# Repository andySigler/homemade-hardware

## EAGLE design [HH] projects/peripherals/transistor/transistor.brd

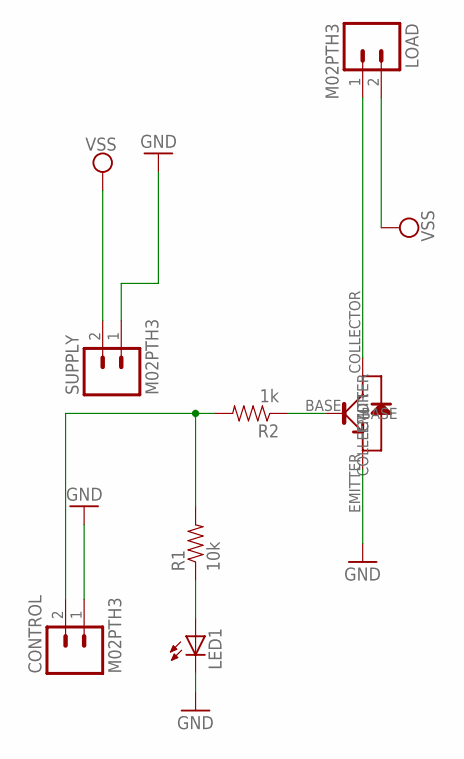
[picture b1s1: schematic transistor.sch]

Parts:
CONTROL: M02PTH3; 1X02_LONGPADS
LED1: LEDCHIPLED_0603; CHIPLED_0603
LOAD: M02PTH3; 1X02_LONGPADS
R1: 10k; 0603-RES
R2: 1k; 0603-RES
SUPPLY: M02PTH3; 1X02_LONGPADS
U$1: STB13007DT4; D2PAK-TO263

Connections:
COLLECTOR: LOAD.1, U$1.COLLECTOR
GND: CONTROL.1, LED1.C, SUPPLY.1, U$1.EMITTER
unnamed: LED1.A, R1.1
unnamed: R2.1, U$1.BASE
unnamed: CONTROL.2, R1.2, R2.2
VSS: LOAD.2, SUPPLY.2

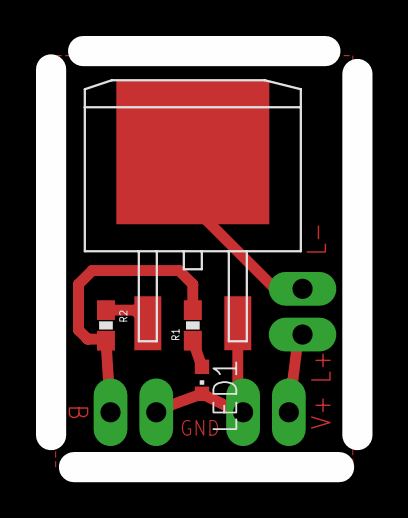
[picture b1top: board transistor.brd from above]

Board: 2 copper layers, 17.0 x 23.1 mm, 7 parts (0 on the bottom side), 6 nets.

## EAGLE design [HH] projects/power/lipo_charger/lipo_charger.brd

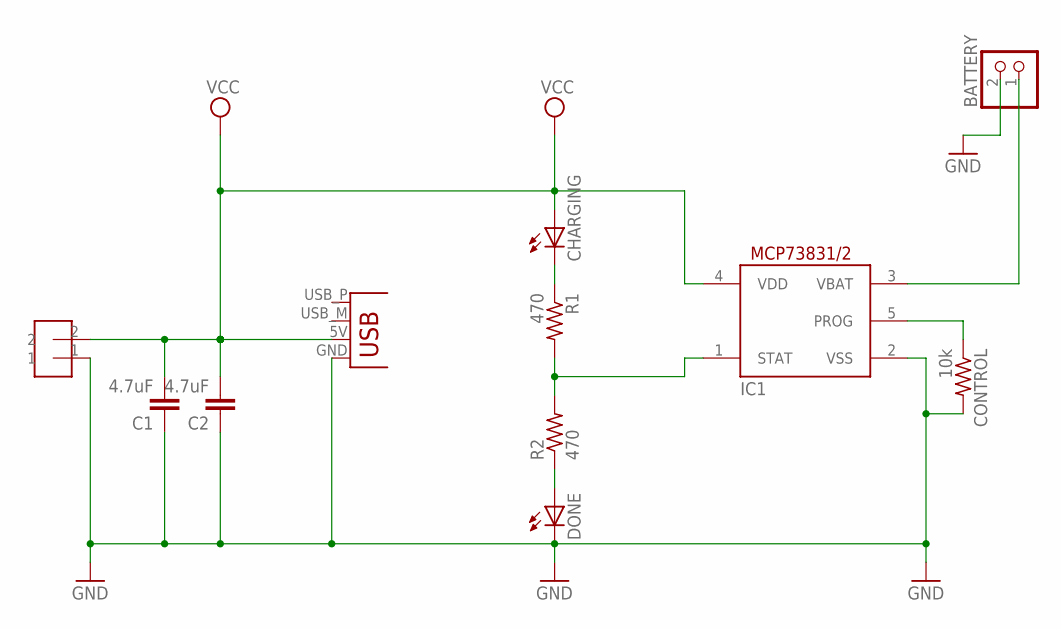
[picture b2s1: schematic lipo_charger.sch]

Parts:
BATTERY: JST_2PIN-SMT-RA; JST-PH-2-SMT-RA
C1, C2: 4.7uF; 0603-CAP
CHARGING: LEDCHIPLED_0603; CHIPLED_0603
CONTROL: 10k; R0603
DONE: LEDCHIPLED_0603; CHIPLED_0603
IC1: MCP73831/OT; SOT23-5L
JP1: USBPCB; USB-A-PCB
R1, R2: 470; R0603
U$1: HEADER-2

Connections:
GND: BATTERY.2 (1), C1.1, C2.1, CONTROL.2, DONE.C, IC1.2 (VSS), JP1.GND, U$1.1
unnamed: IC1.1 (STAT), R1.2, R2.2
unnamed: CHARGING.C, R1.1
unnamed: DONE.A, R2.1
unnamed: BATTERY.1 (2), IC1.3 (VBAT)
unnamed: CONTROL.1, IC1.5 (PROG)
VCC: C1.2, C2.2, CHARGING.A, IC1.4 (VDD), JP1.5V (VBUS), U$1.2

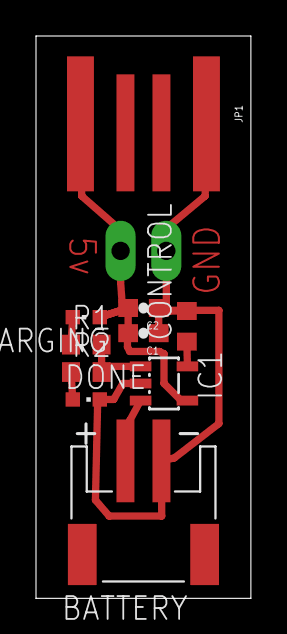
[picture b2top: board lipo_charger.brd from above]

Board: 2 copper layers, 11.9 x 31.2 mm, 11 parts (0 on the bottom side), 7 nets.

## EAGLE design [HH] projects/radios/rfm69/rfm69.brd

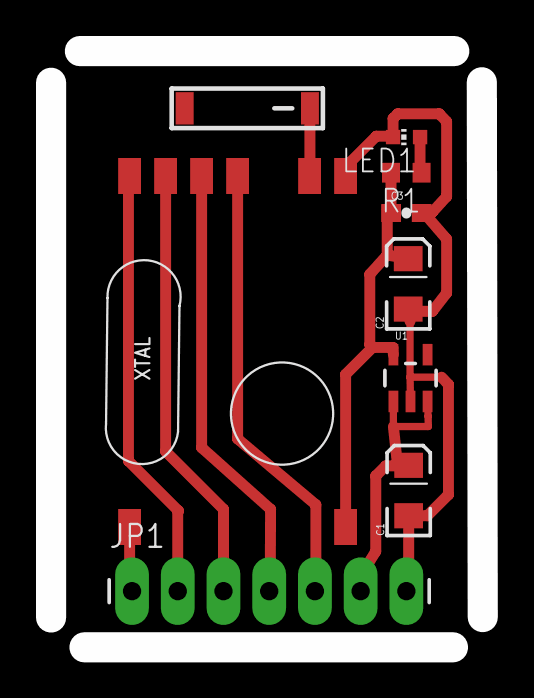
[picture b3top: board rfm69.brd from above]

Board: 2 copper layers, 24.0 x 33.1 mm, 9 parts (0 on the bottom side), 10 nets.

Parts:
C1, C2: EIA3216
C3: 0603-CAP
JP1: 1X07_LONGPADS
LED1: CHIP-LED0603
R1: 10k; R0603
U1: V_REG_LDOSMD; SOT23-5
U$1: 915MHZ-ANTENNA-SMD; 915MHZ-ANTENNA
U$5: RFM69; RFM69W-MINPADS

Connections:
D2: JP1.1, U$5.DIO0
D10_SS: JP1.2, U$5.NSS
D11_MOSI: JP1.3, U$5.MOSI
D12_MISO: JP1.4, U$5.MISO
D13_SCK: JP1.5, U$5.SCK
GND: C1.C, C2.C, C3.2, JP1.7, LED1.C, U1.2, U$5.GND
unnamed: U$1.SIGNAL, U$5.ANA
unnamed: LED1.A, R1.1
VCC: C2.A, C3.1, R1.2, U1.5, U$5.VDD
VSS: C1.A, JP1.6, U1.1, U1.3

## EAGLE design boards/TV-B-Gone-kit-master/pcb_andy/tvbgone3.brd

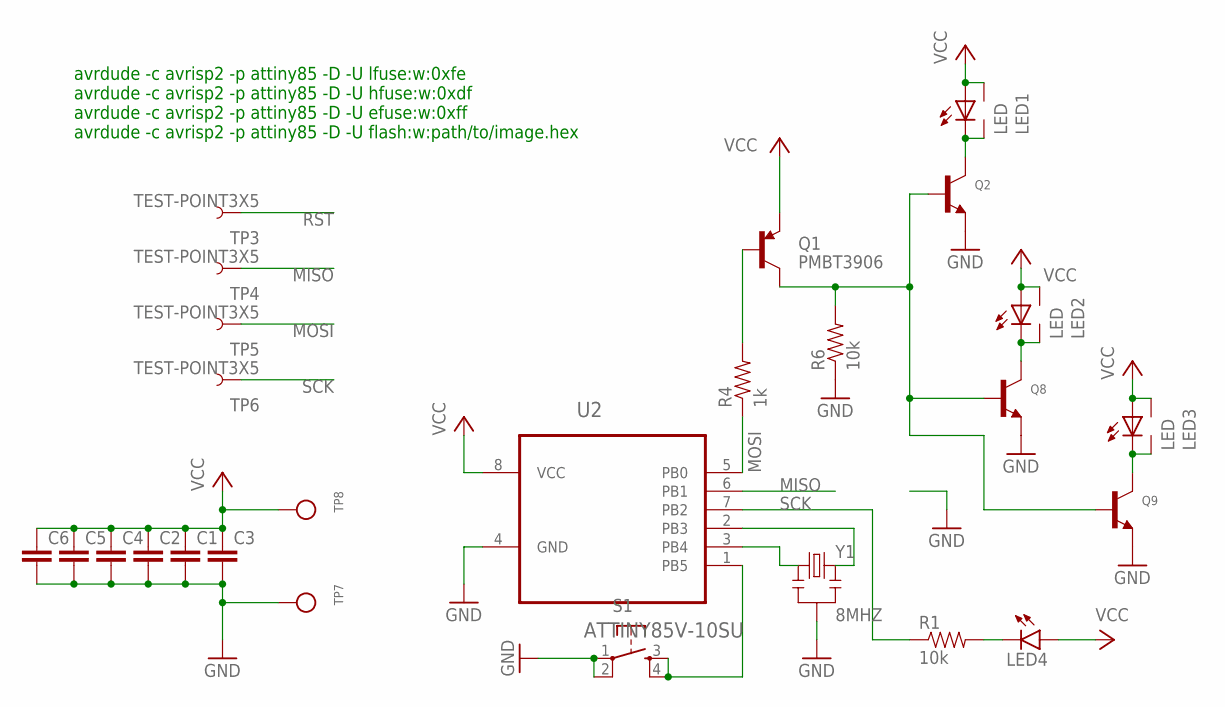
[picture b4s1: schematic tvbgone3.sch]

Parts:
C1, C2, C3, C4, C5, C6: CAP0603-CAP; 0603-CAP
LED1, LED2, LED3: LED; 5MM-SIDE
LED4: LED0603; LED-0603
Q1: PMBT3906; SOT23-3
Q2, Q8, Q9: TRANSISTOR_NPN; SOT-23-R
R1, R6: 10k; 0603-RES
R4: 1k; 0603-RES
S1: TAC_SWITCHSMD; TACTILE-SWITCH-SMD
TP3, TP4, TP5, TP6: TEST-POINT3X5; PAD.03X.05
TP7, TP8: TESTPOINTPAD; TESTPOINT_PAD_2MM
U2: ATTINY85V-10SU; SOIC127P798X216-8N
Y1: 8MHZ; RESONATOR-SMD

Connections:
GND: C1.2, C2.2, C3.2, C4.2, C5.2, C6.2, Q2.3-EMITTER (E), Q8.3-EMITTER (E), Q9.3-EMITTER (E), R6.1, S1.1, S1.2, TP7.P$1, U2.4 (GND), Y1.2
MISO: TP4.P$1, U2.6 (PB1)
MOSI: R4.1, TP5.P$1, U2.5 (PB0)
unnamed: U2.3 (PB4), Y1.1
unnamed: U2.2 (PB3), Y1.3
unnamed: LED4.C, R1.2
unnamed: LED1.K (C), LED1.K2 (C1), Q2.2-COLLECTOR (C)
unnamed: LED2.K (C), LED2.K2 (C1), Q8.2-COLLECTOR (C)
unnamed: Q1.1 (B), R4.2
unnamed: LED3.K (C), LED3.K2 (C1), Q9.2-COLLECTOR (C)
unnamed: Q1.3 (C), Q2.1-BASE (B), Q8.1-BASE (B), Q9.1-BASE (B), R6.2
RST: S1.3, S1.4, TP3.P$1, U2.1 (PB5)
SCK: R1.1, TP6.P$1, U2.7 (PB2)
VCC: C1.1, C2.1, C3.1, C4.1, C5.1, C6.1, LED1.A, LED1.A2 (A1), LED2.A, LED2.A2 (A1), LED3.A, LED3.A2 (A1), LED4.A, Q1.2 (E), TP8.P$1, U2.8 (VCC)

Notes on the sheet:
avrdude -c avrisp2 -p attiny85 -D -U lfuse:w:0xfe avrdude -c avrisp2 -p attiny85 -D -U hfuse:w:0xdf avrdude -c avrisp2 -p attiny85 -D -U efuse:w:0xff avrdude -c avrisp2 -p attiny85 -D -U flash:w:path/to/image.hex

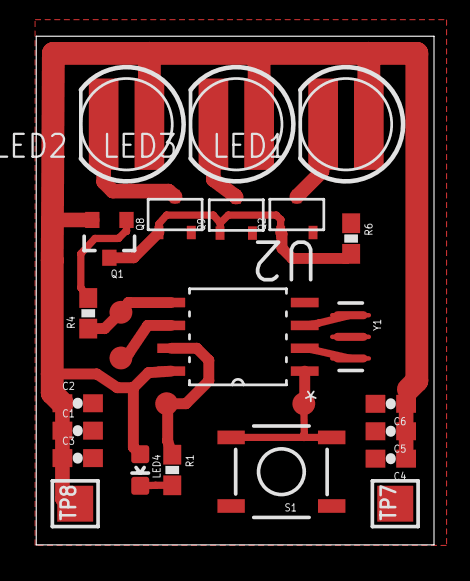
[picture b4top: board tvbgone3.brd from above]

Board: 2 copper layers, 22.1 x 28.3 mm, 26 parts (0 on the bottom side), 14 nets.

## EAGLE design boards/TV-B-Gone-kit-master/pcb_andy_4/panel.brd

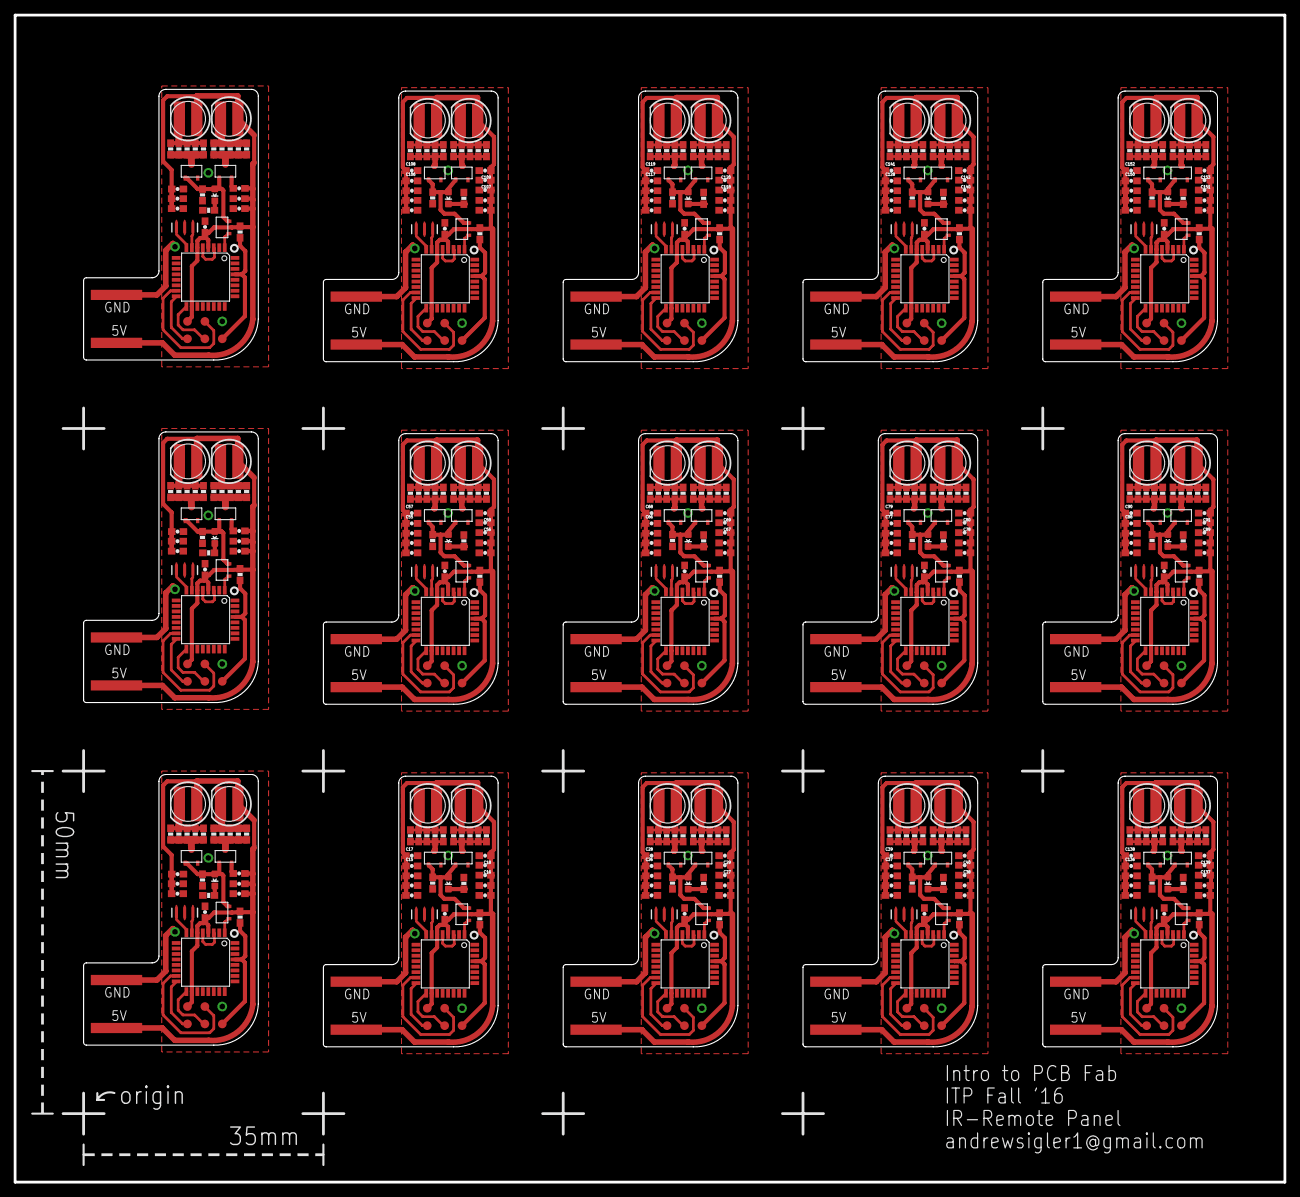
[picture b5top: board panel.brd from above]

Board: 2 copper layers, 185.3 x 170.3 mm, 558 parts (0 on the bottom side), 225 nets.

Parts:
5V, 5V1, 5V2, 5V3, 5V4, 5V5, 5V6, 5V7, 5V8, 5V9, 5V10, 5V11, 5V12, 5V13, 5V14: PAD.03X.05
C1, C2, C3, C4, C5, C6, C8, C10, C11, C12, C13, C14, C15, C16, C17, C18, C19, C21, C22, C23, C24, C25, C26, C27, C28, C29, C30, C32, C33, C34, C35, C36, C37, C38, C39, C40, C41, C43, C44, C45, C46, C47, C48, C50, C51, C52, C53, C54, C55, C56, C57, C58, C59, C61, C62, C63, C64, C65, C66, C67, C68, C69, C70, C72, C73, C74, C75, C76, C77, C78, C79, C80, C81, C83, C84, C85, C86, C87, C88, C89, C90, C91, C92, C94, C95, C96, C97, C98, C99, C101, C102, C103, C104, C105, C106, C107, C108, C109, C110, C112, C113, C114, C115, C116, C117, C118, C119, C120, C121, C123, C124, C125, C126, C127, C128, C129, C131, C132, C133, C134, C135, C136, C137, C138, C139, C140, C141, C142, C143, C145, C146, C147, C148, C149, C150, C151, C152, C153: 4.7uF; 0603-CAP
C7, C9, C20, C31, C42, C49, C60, C71, C82, C93, C100, C111, C122, C130, C144: 0.1uF; 0603-CAP
LED1, LED2, LED3, LED6, LED7, LED9, LED10, LED12, LED13, LED15, LED16, LED18, LED19, LED21, LED22, LED24, LED25, LED27, LED28, LED30, LED31, LED33, LED34, LED36, LED37, LED39, LED40, LED42, LED43, LED45: LED; 5MM-SIDE
LED4, LED5, LED8, LED11, LED14, LED17, LED20, LED23, LED26, LED29, LED32, LED35, LED38, LED41, LED44: LED-0603
MISO, MISO1, MISO2, MISO3, MISO4, MISO5, MISO6, MISO7, MISO8, MISO9, MISO10, MISO11, MISO12, MISO13, MISO14: PAD.03X.05
MOSI, MOSI1, MOSI2, MOSI3, MOSI4, MOSI5, MOSI6, MOSI7, MOSI8, MOSI9, MOSI10, MOSI11, MOSI12, MOSI13, MOSI14: PAD.03X.05
Q1, Q2, Q3, Q4, Q5, Q6, Q7, Q8, Q9, Q10, Q11, Q12, Q13, Q14, Q15, Q16, Q17, Q18, Q19, Q20, Q21, Q22, Q23, Q24, Q25, Q26, Q27, Q28, Q29, Q30, Q31, Q32, Q33, Q34, Q35, Q36, Q37, Q38, Q39, Q40, Q41, Q42, Q43, Q44, Q45: SOT-23-R
R1, R15, R28, R41, R54, R67, R80, R93, R106, R119, R132, R145, R158, R171, R184: 1k; 0603-RES
R2, R3, R4, R7, R8, R9, R10, R11, R12, R13, R17, R18, R19, R20, R21, R22, R23, R24, R25, R26, R30, R31, R32, R33, R34, R35, R36, R37, R38, R39, R43, R44, R45, R46, R47, R48, R49, R50, R51, R52, R56, R57, R58, R59, R60, R61, R62, R63, R64, R65, R69, R70, R71, R72, R73, R74, R75, R76, R77, R78, R82, R83, R84, R85, R86, R87, R88, R89, R90, R91, R95, R96, R97, R98, R99, R100, R101, R102, R103, R104, R108, R109, R110, R111, R112, R113, R114, R115, R116, R117, R121, R122, R123, R124, R125, R126, R127, R128, R129, R130, R134, R135, R136, R137, R138, R139, R140, R141, R142, R143, R147, R148, R149, R150, R151, R152, R153, R154, R155, R156, R160, R161, R162, R163, R164, R165, R166, R167, R168, R169, R173, R174, R175, R176, R177, R178, R179, R180, R181, R182, R186, R187, R188, R189, R190, R191, R192, R193, R194, R195: 100; 0603-RES
R5, R6, R14, R16, R27, R29, R40, R42, R53, R55, R66, R68, R79, R81, R92, R94, R105, R107, R118, R120, R131, R133, R144, R146, R157, R159, R170, R172, R183, R185: 10k; 0603-RES
RST, RST1, RST2, RST3, RST4, RST5, RST6, RST7, RST8, RST9, RST10, RST11, RST12, RST13, RST14: PAD.03X.05
SCK, SCK1, SCK2, SCK3, SCK4, SCK5, SCK6, SCK7, SCK8, SCK9, SCK10, SCK11, SCK12, SCK13, SCK14: PAD.03X.05
U1, U2, U3, U4, U5, U6, U7, U8, U9, U10, U11, U12, U13, U14, U15: ATMEGA328P; TQFP32-08
U$1, U$2, U$3, U$4, U$5, U$6, U$7, U$8, U$9, U$10, U$11, U$12, U$13, U$14, U$15: USB-POWER-ONLY; USB-A-PCB-POWER-ONLY
Y1, Y2, Y3, Y4, Y5, Y6, Y7, Y8, Y9, Y10, Y11, Y12, Y13, Y14, Y15: 18MHZ; RESONATOR-SMD

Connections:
GND: C1.2, C2.2, C3.2, C4.2, C5.2, C6.2, C7.2, Q2.3-EMITTER, Q9.3-EMITTER, R1.1, R6.1, U1.3, U1.5, U1.21, U$1.GND, Y1.2
GND2: C129.2, C130.2, C131.2, C132.2, C133.2, C134.2, C135.2, C136.2, C137.2, C138.2, C139.2, Q37.3-EMITTER, Q38.3-EMITTER, R157.1, R158.1, U13.3, U13.5, U13.21, U$13.GND, Y13.2
GND3: C41.2, C42.2, C43.2, C44.2, C45.2, C46.2, C47.2, Q13.3-EMITTER, Q14.3-EMITTER, R53.1, R54.1, U5.3, U5.5, U5.21, U$5.GND, Y5.2
GND4: C48.2, C49.2, C50.2, C51.2, C52.2, C53.2, C54.2, C55.2, C56.2, C57.2, C58.2, Q16.3-EMITTER, Q17.3-EMITTER, R66.1, R67.1, U6.3, U6.5, U6.21, U$6.GND, Y6.2
GND5: C59.2, C60.2, C61.2, C62.2, C63.2, C64.2, C65.2, C66.2, C67.2, C68.2, C69.2, Q19.3-EMITTER, Q20.3-EMITTER, R79.1, R80.1, U7.3, U7.5, U7.21, U$7.GND, Y7.2
GND6: C70.2, C71.2, C72.2, C73.2, C74.2, C75.2, C76.2, C77.2, C78.2, C79.2, C80.2, Q22.3-EMITTER, Q23.3-EMITTER, R92.1, R93.1, U8.3, U8.5, U8.21, U$8.GND, Y8.2
GND7: C81.2, C82.2, C83.2, C84.2, C85.2, C86.2, C87.2, C88.2, C89.2, C90.2, C91.2, Q25.3-EMITTER, Q26.3-EMITTER, R105.1, R106.1, U9.3, U9.5, U9.21, U$9.GND, Y9.2
GND8: C92.2, C93.2, C94.2, C95.2, C96.2, C97.2, C98.2, Q28.3-EMITTER, Q29.3-EMITTER, R118.1, R119.1, U10.3, U10.5, U10.21, U$10.GND, Y10.2
GND9: C99.2, C100.2, C101.2, C102.2, C103.2, C104.2, C105.2, C106.2, C107.2, C108.2, C109.2, Q31.3-EMITTER, Q32.3-EMITTER, R131.1, R132.1, U11.3, U11.5, U11.21, U$11.GND, Y11.2
GND10: C110.2, C111.2, C112.2, C113.2, C114.2, C115.2, C116.2, C117.2, C118.2, C119.2, C120.2, Q34.3-EMITTER, Q35.3-EMITTER, R144.1, R145.1, U12.3, U12.5, U12.21, U$12.GND, Y12.2
GND11: C121.2, C122.2, C123.2, C124.2, C125.2, C126.2, C127.2, C128.2, C140.2, C141.2, C142.2, Q40.3-EMITTER, Q41.3-EMITTER, R170.1, R171.1, U14.3, U14.5, U14.21, U$14.GND, Y14.2
GND12: C143.2, C144.2, C145.2, C146.2, C147.2, C148.2, C149.2, C150.2, C151.2, C152.2, C153.2, Q43.3-EMITTER, Q44.3-EMITTER, R183.1, R184.1, U15.3, U15.5, U15.21, U$15.GND, Y15.2
GND13: C8.2, C9.2, C10.2, C11.2, C12.2, C13.2, C14.2, C15.2, C16.2, C17.2, C18.2, Q3.3-EMITTER, Q4.3-EMITTER, R14.1, R15.1, U2.3, U2.5, U2.21, U$2.GND, Y2.2
GND14: C19.2, C20.2, C21.2, C22.2, C23.2, C24.2, C25.2, C26.2, C27.2, C28.2, C29.2, Q6.3-EMITTER, Q7.3-EMITTER, R27.1, R28.1, U3.3, U3.5, U3.21, U$3.GND, Y3.2
GND15: C30.2, C31.2, C32.2, C33.2, C34.2, C35.2, C36.2, C37.2, C38.2, C39.2, C40.2, Q10.3-EMITTER, Q11.3-EMITTER, R40.1, R41.1, U4.3, U4.5, U4.21, U$4.GND, Y4.2
MISO: MISO.P$1, U1.16
MISO1: MISO1.P$1, U2.16
MISO2: MISO2.P$1, U3.16
MISO3: MISO3.P$1, U4.16
MISO4: MISO4.P$1, U5.16
MISO5: MISO5.P$1, U6.16
MISO6: MISO6.P$1, U7.16
MISO7: MISO7.P$1, U8.16
MISO8: MISO8.P$1, U9.16
MISO9: MISO9.P$1, U10.16
MISO10: MISO10.P$1, U11.16
MISO11: MISO11.P$1, U12.16
MISO12: MISO12.P$1, U13.16
MISO13: MISO13.P$1, U14.16
MISO14: MISO14.P$1, U15.16
MOSI: MOSI.P$1, U1.15
MOSI1: MOSI1.P$1, U2.15
MOSI2: MOSI2.P$1, U3.15
MOSI3: MOSI3.P$1, U4.15
MOSI4: MOSI4.P$1, U5.15
MOSI5: MOSI5.P$1, U6.15
MOSI6: MOSI6.P$1, U7.15
MOSI7: MOSI7.P$1, U8.15
MOSI8: MOSI8.P$1, U9.15
MOSI9: MOSI9.P$1, U10.15
MOSI10: MOSI10.P$1, U11.15
MOSI11: MOSI11.P$1, U12.15
MOSI12: MOSI12.P$1, U13.15
MOSI13: MOSI13.P$1, U14.15
MOSI14: MOSI14.P$1, U15.15
unnamed: U1.8, Y1.3
unnamed: U1.7, Y1.1
unnamed: LED4.C, R1.2
unnamed: Q2.2-COLLECTOR, R9.1, R10.1, R11.1, R12.1, R13.1
unnamed: U2.8, Y2.3
unnamed: Q1.1-BASE, U1.1
unnamed: U2.7, Y2.1
unnamed: LED1.K, R9.2, R10.2, R11.2, R12.2, R13.2
unnamed: Q5.1-BASE, U2.1
unnamed: LED4.A, Q1.3-EMITTER, Q2.1-BASE, Q9.1-BASE, R6.2
unnamed: Q9.2-COLLECTOR, R2.1, R3.1, R4.1, R7.1, R8.1
unnamed: LED3.K, R2.2, R3.2, R4.2, R7.2, R8.2
unnamed: LED5.A, Q3.1-BASE, Q4.1-BASE, Q5.3-EMITTER, R14.2
unnamed: LED5.C, R15.2
unnamed: Q3.2-COLLECTOR, R17.1, R18.1, R19.1, R20.1, R21.1
unnamed: LED2.K, R17.2, R18.2, R19.2, R20.2, R21.2
unnamed: Q4.2-COLLECTOR, R22.1, R23.1, R24.1, R25.1, R26.1
unnamed: LED6.K, R22.2, R23.2, R24.2, R25.2, R26.2
unnamed: U3.8, Y3.3
unnamed: U3.7, Y3.1
unnamed: Q8.1-BASE, U3.1
unnamed: LED8.A, Q6.1-BASE, Q7.1-BASE, Q8.3-EMITTER, R27.2
unnamed: LED8.C, R28.2
unnamed: Q6.2-COLLECTOR, R30.1, R31.1, R32.1, R33.1, R34.1
unnamed: LED7.K, R30.2, R31.2, R32.2, R33.2, R34.2
unnamed: Q7.2-COLLECTOR, R35.1, R36.1, R37.1, R38.1, R39.1
unnamed: LED9.K, R35.2, R36.2, R37.2, R38.2, R39.2
unnamed: U4.8, Y4.3
unnamed: U4.7, Y4.1
unnamed: Q12.1-BASE, U4.1
unnamed: LED11.A, Q10.1-BASE, Q11.1-BASE, Q12.3-EMITTER, R40.2
unnamed: LED11.C, R41.2
unnamed: Q10.2-COLLECTOR, R43.1, R44.1, R45.1, R46.1, R47.1
unnamed: LED10.K, R43.2, R44.2, R45.2, R46.2, R47.2
unnamed: Q11.2-COLLECTOR, R48.1, R49.1, R50.1, R51.1, R52.1
unnamed: LED12.K, R48.2, R49.2, R50.2, R51.2, R52.2
unnamed: U5.8, Y5.3
unnamed: U5.7, Y5.1
unnamed: Q15.1-BASE, U5.1
unnamed: LED14.A, Q13.1-BASE, Q14.1-BASE, Q15.3-EMITTER, R53.2
unnamed: LED14.C, R54.2
unnamed: Q13.2-COLLECTOR, R56.1, R57.1, R58.1, R59.1, R60.1
unnamed: LED13.K, R56.2, R57.2, R58.2, R59.2, R60.2
unnamed: Q14.2-COLLECTOR, R61.1, R62.1, R63.1, R64.1, R65.1
unnamed: LED15.K, R61.2, R62.2, R63.2, R64.2, R65.2
unnamed: U6.8, Y6.3
unnamed: U6.7, Y6.1
unnamed: Q18.1-BASE, U6.1
unnamed: LED17.A, Q16.1-BASE, Q17.1-BASE, Q18.3-EMITTER, R66.2
unnamed: LED17.C, R67.2
unnamed: Q16.2-COLLECTOR, R69.1, R70.1, R71.1, R72.1, R73.1
unnamed: LED16.K, R69.2, R70.2, R71.2, R72.2, R73.2
unnamed: Q17.2-COLLECTOR, R74.1, R75.1, R76.1, R77.1, R78.1
unnamed: LED18.K, R74.2, R75.2, R76.2, R77.2, R78.2
unnamed: U7.8, Y7.3
unnamed: U7.7, Y7.1
unnamed: Q21.1-BASE, U7.1
unnamed: LED20.A, Q19.1-BASE, Q20.1-BASE, Q21.3-EMITTER, R79.2
unnamed: LED20.C, R80.2
unnamed: Q19.2-COLLECTOR, R82.1, R83.1, R84.1, R85.1, R86.1
unnamed: LED19.K, R82.2, R83.2, R84.2, R85.2, R86.2
unnamed: Q20.2-COLLECTOR, R87.1, R88.1, R89.1, R90.1, R91.1
unnamed: LED21.K, R87.2, R88.2, R89.2, R90.2, R91.2
unnamed: U8.8, Y8.3
unnamed: U8.7, Y8.1
unnamed: Q24.1-BASE, U8.1
unnamed: LED23.A, Q22.1-BASE, Q23.1-BASE, Q24.3-EMITTER, R92.2
unnamed: LED23.C, R93.2
unnamed: Q22.2-COLLECTOR, R95.1, R96.1, R97.1, R98.1, R99.1
unnamed: LED22.K, R95.2, R96.2, R97.2, R98.2, R99.2
unnamed: Q23.2-COLLECTOR, R100.1, R101.1, R102.1, R103.1, R104.1
unnamed: LED24.K, R100.2, R101.2, R102.2, R103.2, R104.2
unnamed: U9.8, Y9.3
unnamed: U9.7, Y9.1
unnamed: Q27.1-BASE, U9.1
unnamed: LED26.A, Q25.1-BASE, Q26.1-BASE, Q27.3-EMITTER, R105.2
unnamed: LED26.C, R106.2
unnamed: Q25.2-COLLECTOR, R108.1, R109.1, R110.1, R111.1, R112.1
unnamed: LED25.K, R108.2, R109.2, R110.2, R111.2, R112.2
unnamed: Q26.2-COLLECTOR, R113.1, R114.1, R115.1, R116.1, R117.1
unnamed: LED27.K, R113.2, R114.2, R115.2, R116.2, R117.2
unnamed: U10.8, Y10.3
unnamed: U10.7, Y10.1
unnamed: Q30.1-BASE, U10.1
unnamed: LED29.A, Q28.1-BASE, Q29.1-BASE, Q30.3-EMITTER, R118.2
unnamed: LED29.C, R119.2
unnamed: Q28.2-COLLECTOR, R121.1, R122.1, R123.1, R124.1, R125.1
unnamed: LED28.K, R121.2, R122.2, R123.2, R124.2, R125.2
unnamed: Q29.2-COLLECTOR, R126.1, R127.1, R128.1, R129.1, R130.1
unnamed: LED30.K, R126.2, R127.2, R128.2, R129.2, R130.2
unnamed: U11.8, Y11.3
unnamed: U11.7, Y11.1
unnamed: Q33.1-BASE, U11.1
unnamed: LED32.A, Q31.1-BASE, Q32.1-BASE, Q33.3-EMITTER, R131.2
unnamed: LED32.C, R132.2
unnamed: Q31.2-COLLECTOR, R134.1, R135.1, R136.1, R137.1, R138.1
unnamed: LED31.K, R134.2, R135.2, R136.2, R137.2, R138.2
unnamed: Q32.2-COLLECTOR, R139.1, R140.1, R141.1, R142.1, R143.1
unnamed: LED33.K, R139.2, R140.2, R141.2, R142.2, R143.2
unnamed: U12.8, Y12.3
unnamed: U12.7, Y12.1
unnamed: Q36.1-BASE, U12.1
unnamed: LED35.A, Q34.1-BASE, Q35.1-BASE, Q36.3-EMITTER, R144.2
unnamed: LED35.C, R145.2
unnamed: Q34.2-COLLECTOR, R147.1, R148.1, R149.1, R150.1, R151.1
unnamed: LED34.K, R147.2, R148.2, R149.2, R150.2, R151.2
unnamed: Q35.2-COLLECTOR, R152.1, R153.1, R154.1, R155.1, R156.1
unnamed: LED36.K, R152.2, R153.2, R154.2, R155.2, R156.2
unnamed: U13.8, Y13.3
unnamed: U13.7, Y13.1
unnamed: Q39.1-BASE, U13.1
unnamed: LED38.A, Q37.1-BASE, Q38.1-BASE, Q39.3-EMITTER, R157.2
unnamed: LED38.C, R158.2
unnamed: Q37.2-COLLECTOR, R160.1, R161.1, R162.1, R163.1, R164.1
unnamed: LED37.K, R160.2, R161.2, R162.2, R163.2, R164.2
unnamed: Q38.2-COLLECTOR, R165.1, R166.1, R167.1, R168.1, R169.1
unnamed: LED39.K, R165.2, R166.2, R167.2, R168.2, R169.2
unnamed: U14.8, Y14.3
unnamed: U14.7, Y14.1
unnamed: Q42.1-BASE, U14.1
unnamed: LED41.A, Q40.1-BASE, Q41.1-BASE, Q42.3-EMITTER, R170.2
unnamed: LED41.C, R171.2
unnamed: Q40.2-COLLECTOR, R173.1, R174.1, R175.1, R176.1, R177.1
unnamed: LED40.K, R173.2, R174.2, R175.2, R176.2, R177.2
unnamed: Q41.2-COLLECTOR, R178.1, R179.1, R180.1, R181.1, R182.1
unnamed: LED42.K, R178.2, R179.2, R180.2, R181.2, R182.2
unnamed: U15.8, Y15.3
unnamed: U15.7, Y15.1
unnamed: Q45.1-BASE, U15.1
unnamed: LED44.A, Q43.1-BASE, Q44.1-BASE, Q45.3-EMITTER, R183.2
unnamed: LED44.C, R184.2
unnamed: Q43.2-COLLECTOR, R186.1, R187.1, R188.1, R189.1, R190.1
unnamed: LED43.K, R186.2, R187.2, R188.2, R189.2, R190.2
unnamed: Q44.2-COLLECTOR, R191.1, R192.1, R193.1, R194.1, R195.1
unnamed: LED45.K, R191.2, R192.2, R193.2, R194.2, R195.2
RST: R5.2, RST.P$1, U1.29
RST1: R16.2, RST1.P$1, U2.29
RST2: R29.2, RST2.P$1, U3.29
RST3: R42.2, RST3.P$1, U4.29
RST4: R55.2, RST4.P$1, U5.29
RST5: R68.2, RST5.P$1, U6.29
RST6: R81.2, RST6.P$1, U7.29
RST7: R94.2, RST7.P$1, U8.29
RST8: R107.2, RST8.P$1, U9.29
RST9: R120.2, RST9.P$1, U10.29
RST10: R133.2, RST10.P$1, U11.29
RST11: R146.2, RST11.P$1, U12.29
RST12: R159.2, RST12.P$1, U13.29
RST13: R172.2, RST13.P$1, U14.29
RST14: R185.2, RST14.P$1, U15.29
SCK: SCK.P$1, U1.17
SCK1: SCK1.P$1, U2.17
SCK2: SCK2.P$1, U3.17
SCK3: SCK3.P$1, U4.17
SCK4: SCK4.P$1, U5.17
SCK5: SCK5.P$1, U6.17
SCK6: SCK6.P$1, U7.17
SCK7: SCK7.P$1, U8.17
SCK8: SCK8.P$1, U9.17
SCK9: SCK9.P$1, U10.17
SCK10: SCK10.P$1, U11.17
SCK11: SCK11.P$1, U12.17
SCK12: SCK12.P$1, U13.17
SCK13: SCK13.P$1, U14.17
SCK14: SCK14.P$1, U15.17
VCC: 5V.P$1, C1.1, C2.1, C3.1, C4.1, C5.1, C6.1, C7.1, LED1.A, LED3.A, Q1.2-COLLECTOR, R5.1, U1.4, U1.6, U1.18, U$1.5V
VCC1: 5V1.P$1, C8.1, C9.1, C10.1, C11.1, C12.1, C13.1, C14.1, C15.1, C16.1, C17.1, C18.1, LED2.A, LED6.A, Q5.2-COLLECTOR, R16.1, U2.4, U2.6, U2.18, U$2.5V
VCC2: 5V2.P$1, C19.1, C20.1, C21.1, C22.1, C23.1, C24.1, C25.1, C26.1, C27.1, C28.1, C29.1, LED7.A, LED9.A, Q8.2-COLLECTOR, R29.1, U3.4, U3.6, U3.18, U$3.5V
VCC3: 5V3.P$1, C30.1, C31.1, C32.1, C33.1, C34.1, C35.1, C36.1, C37.1, C38.1, C39.1, C40.1, LED10.A, LED12.A, Q12.2-COLLECTOR, R42.1, U4.4, U4.6, U4.18, U$4.5V
VCC4: 5V4.P$1, C41.1, C42.1, C43.1, C44.1, C45.1, C46.1, C47.1, LED13.A, LED15.A, Q15.2-COLLECTOR, R55.1, U5.4, U5.6, U5.18, U$5.5V
VCC5: 5V5.P$1, C48.1, C49.1, C50.1, C51.1, C52.1, C53.1, C54.1, C55.1, C56.1, C57.1, C58.1, LED16.A, LED18.A, Q18.2-COLLECTOR, R68.1, U6.4, U6.6, U6.18, U$6.5V
VCC6: 5V6.P$1, C59.1, C60.1, C61.1, C62.1, C63.1, C64.1, C65.1, C66.1, C67.1, C68.1, C69.1, LED19.A, LED21.A, Q21.2-COLLECTOR, R81.1, U7.4, U7.6, U7.18, U$7.5V
VCC7: 5V7.P$1, C70.1, C71.1, C72.1, C73.1, C74.1, C75.1, C76.1, C77.1, C78.1, C79.1, C80.1, LED22.A, LED24.A, Q24.2-COLLECTOR, R94.1, U8.4, U8.6, U8.18, U$8.5V
VCC8: 5V8.P$1, C81.1, C82.1, C83.1, C84.1, C85.1, C86.1, C87.1, C88.1, C89.1, C90.1, C91.1, LED25.A, LED27.A, Q27.2-COLLECTOR, R107.1, U9.4, U9.6, U9.18, U$9.5V
VCC9: 5V9.P$1, C92.1, C93.1, C94.1, C95.1, C96.1, C97.1, C98.1, LED28.A, LED30.A, Q30.2-COLLECTOR, R120.1, U10.4, U10.6, U10.18, U$10.5V
VCC10: 5V10.P$1, C99.1, C100.1, C101.1, C102.1, C103.1, C104.1, C105.1, C106.1, C107.1, C108.1, C109.1, LED31.A, LED33.A, Q33.2-COLLECTOR, R133.1, U11.4, U11.6, U11.18, U$11.5V
VCC11: 5V11.P$1, C110.1, C111.1, C112.1, C113.1, C114.1, C115.1, C116.1, C117.1, C118.1, C119.1, C120.1, LED34.A, LED36.A, Q36.2-COLLECTOR, R146.1, U12.4, U12.6, U12.18, U$12.5V
VCC12: 5V12.P$1, C129.1, C130.1, C131.1, C132.1, C133.1, C134.1, C135.1, C136.1, C137.1, C138.1, C139.1, LED37.A, LED39.A, Q39.2-COLLECTOR, R159.1, U13.4, U13.6, U13.18, U$13.5V
VCC13: 5V13.P$1, C121.1, C122.1, C123.1, C124.1, C125.1, C126.1, C127.1, C128.1, C140.1, C141.1, C142.1, LED40.A, LED42.A, Q42.2-COLLECTOR, R172.1, U14.4, U14.6, U14.18, U$14.5V
VCC14: 5V14.P$1, C143.1, C144.1, C145.1, C146.1, C147.1, C148.1, C149.1, C150.1, C151.1, C152.1, C153.1, LED43.A, LED45.A, Q45.2-COLLECTOR, R185.1, U15.4, U15.6, U15.18, U$15.5V

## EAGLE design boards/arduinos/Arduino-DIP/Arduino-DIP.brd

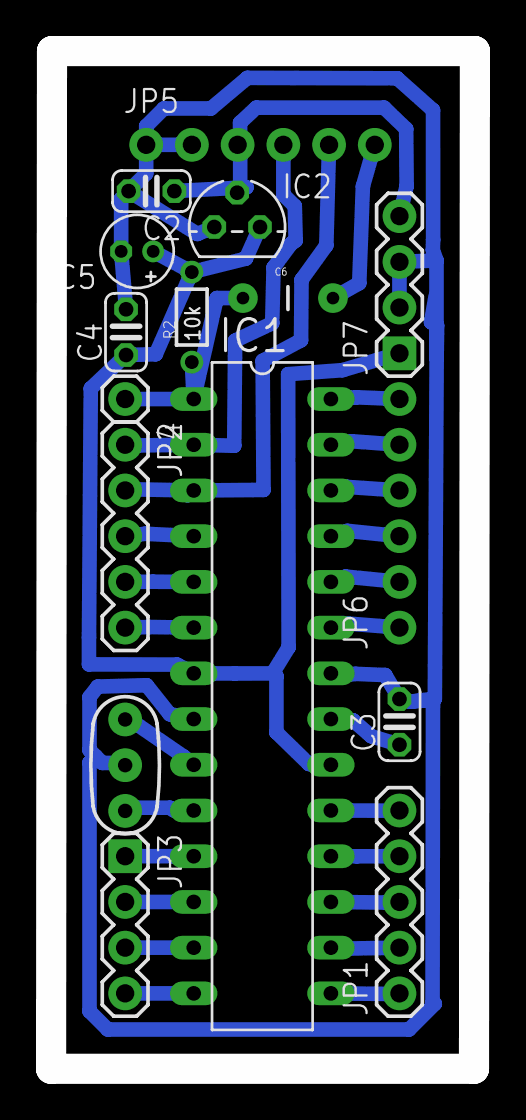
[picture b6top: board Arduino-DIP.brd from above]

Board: 2 copper layers, 23.5 x 56.5 mm, 16 parts (0 on the bottom side), 28 nets.

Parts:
C2, C3, C4: 0.1µ; C025-024X044
C5: 10µ; E1,8-4
C6: 0.1uF; CAP-PTH-5MM
IC1: ATMEGA 328; DIL28-3
IC2: MCP1702-33; TO92
JP1, JP2: 1X05
JP3, JP7: 1X04
JP4: M01PTH; 1X01
JP5, JP6: 1X06_NO_SILK
R2: 10k; 1/6W-RES
X1: 16 MHz; RESONATOR-PTH

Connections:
GND: C2.2, C3.2, C4.2, C5.-, IC1.8, IC1.22, IC2.1, JP5.1, JP5.2, JP7.2, JP7.3, X1.2
unnamed: IC1.9, X1.1
unnamed: IC1.23, JP6.1
unnamed: IC1.24, JP6.2
unnamed: IC1.25, JP6.3
unnamed: IC1.26, JP6.4
unnamed: IC1.27, JP6.5
unnamed: IC1.28, JP6.6
unnamed: IC1.4, JP2.3
unnamed: IC1.5, JP2.4
unnamed: IC1.6, JP2.5
unnamed: IC1.11, JP3.1
unnamed: IC1.12, JP3.2
unnamed: IC1.13, JP3.3
unnamed: IC1.14, JP3.4
unnamed: IC1.15, JP1.1
unnamed: IC1.16, JP1.2
unnamed: IC1.17, JP1.3
unnamed: IC1.18, JP1.4
unnamed: C3.1, IC1.21
unnamed: C6.2, JP5.6
unnamed: IC1.10, X1.3
unnamed: IC1.19, JP1.5
PWR: C2.1, IC2.2, JP5.3, JP7.4
RST: C6.1, IC1.1, JP4.1, R2.1
RXD: IC1.2, JP2.1, JP5.4
TXD: IC1.3, JP2.2, JP5.5
VCC: C4.1, C5.+, IC1.7, IC1.20, IC2.3, JP7.1, R2.2

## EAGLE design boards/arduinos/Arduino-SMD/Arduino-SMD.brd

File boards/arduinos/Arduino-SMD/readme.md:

#Homemade SMD Microcontroller
##A clone of the Arduino-Pro-Mini

This is a redesign of the [Arduino Pro Mini](http://arduino.cc/en/Main/arduinoBoardProMini), which uses the Uno Bootloader. The design is constrained by rapid prototyping tools and processes used to make the PCB. The most notabe constraints are micro-milling machines and DIY vias.

###Features

* Bootloader: Arduino Uno
* Specs: 3.3 volts @ 16MHz
* Dimension: 3.5cm x 2cm (1.37" x 0.8")
* Onboard LED on Digital Pin 5 (not 13)
* FTDI programming headers
* Onboard reset button
* Solder points for [coin cell battery holder](http://www.digikey.com/product-detail/en/BA2032/BA2032-ND/257744)

###Pinouts

###Building

The board is designed to be milled on a micro-milling machine from copper clad plates. The job requires:
* 1/64" and 1/32" endmill to form routes
* 18 and 22 gauge drill bits for vias and holes
* 1/16" endmill for the dimension

Toolpath lines are drawn with the `wire` command on `.brd` layers `114`, `115`, `117`, and `118`.

Dynamask solder mask is then applied, and the board is exposed in a homemade UV lightbox for 45 seconds. This exposure is made through transparency film with the `.brd` `tStop` and `bStop` printed in black.

Vias are filled with solid 24 gauge wire, bent at 90 degree angles on either side to prevent them from falling out. Solder paste is then applied to the vias, and reflowed to make connections between the top and bottom.

###Parts List

* [ATMega328](http://www.digikey.com/product-detail/en/ATMEGA328-AUR/ATMEGA328-AURCT-ND/3440951) (this build does not use the more popular [ATMega328p](http://www.digikey.com/product-detail/en/ATMEGA328P-AUR/ATMEGA328P-AURCT-ND/3789455))
* [3.3 Volt Regulator](http://www.digikey.com/product-detail/en/MIC5205-3.3YM5%20TR/576-1259-1-ND/771886)
* [16 MHz Resonator](http://www.digikey.com/product-detail/en/PRQC16.00SR1010V00L/1253-1339-1-ND/4879394)
* [10 uF Pol. Capacitor](http://www.digikey.com/product-detail/en/T491A106K006AT7280/399-10116-1-ND/3759233) x 2
* [0.1 uF Capacitor](http://www.digikey.com/product-detail/en/CC0603ZRY5V9BB104/311-1343-1-ND/2103127) x 3
* [10,000 Ohm Resistor](http://www.digikey.com/product-detail/en/RC0603JR-0710KL/311-10KGRCT-ND/729647) x 3
* [LED](http://www.digikey.com/product-search/en?pv7=2&k=160-1434-2-ND&mnonly=0&newproducts=0&ColumnSort=0&page=1&quantity=0&ptm=0&fid=0&pageSize=25) x 2
* [Tactile Switch](http://www.digikey.com/product-detail/en/8-1437565-1/450-1941-ND/529677)
* [Coin Cell Battery Holder](http://www.digikey.com/product-detail/en/BA2032/BA2032-ND/257744) (optional)

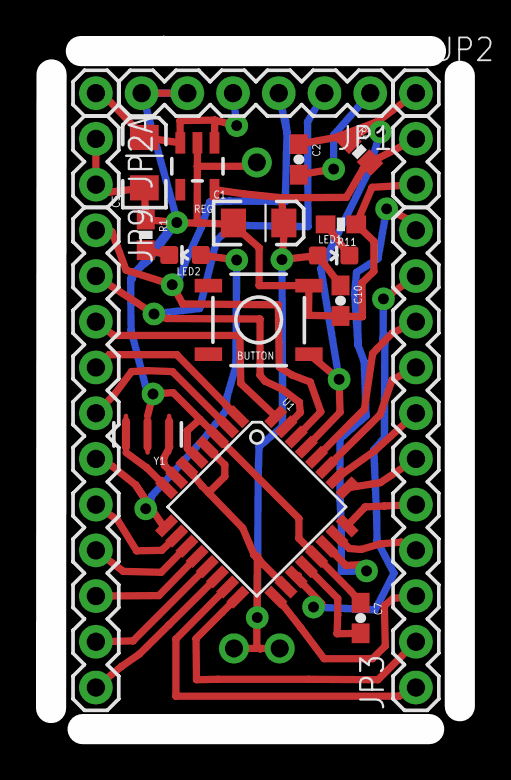
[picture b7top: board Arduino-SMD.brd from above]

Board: 2 copper layers, 22.7 x 37.7 mm, 22 parts (1 on the bottom side), 32 nets.

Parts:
BUTTON: Button; TACTILE-SWITCH-SMD
C1, C5: 10uF; EIA3216
C2, C7, C10: 0.1uF; 0603-CAP
JP1: FTDI Basic; 1X06
JP2, JP4: M01PTH; 1X01
JP2A, JP2A1: M02PTH; 1X02
JP3, JP9: M11PTH; 1X11
LED1, LED2: Red; 0603-LED-ALT1
R1, R2, R11: 10K; 0603-RES
REG: 3.3V; SOT23-5
U1: ATMEGA328P; TQFP32-08
U$1: BATTERY-ITP; BATTCOM_20MM_PTH
Y1: 8MHZ; RESONATOR-SMD

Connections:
DTR: C2.2, JP1.1
GND: BUTTON.3, C1.C, C5.C, C7.1, C10.2, JP1.5, JP1.6, JP2A.1, JP2A.2, JP2A1.2, R1.1, R11.1, REG.2, U1.3, U1.5, U1.21, U$1.GND, Y1.2
unnamed: U1.8, Y1.3
unnamed: U1.7, Y1.1
unnamed: LED1.C, R11.2
unnamed: JP3.1, U1.15
unnamed: JP3.2, U1.16
unnamed: JP3.3, U1.17
unnamed: JP3.11, U1.22
unnamed: JP3.10, U1.19
unnamed: JP3.9, U1.28
unnamed: JP3.8, U1.27
unnamed: JP3.7, U1.26
unnamed: JP3.6, U1.25
unnamed: JP3.5, U1.24
unnamed: JP3.4, U1.23
unnamed: LED2.C, R1.2
unnamed: JP9.7, U1.10
unnamed: C5.A, JP1.4, JP4.1, REG.1, REG.3
unnamed: JP9.3, U1.32
unnamed: C7.2, U1.20
unnamed: JP9.4, U1.1
unnamed: JP9.5, U1.2
unnamed: JP9.6, LED2.A, U1.9
unnamed: JP9.8, U1.11
unnamed: JP9.9, U1.12
unnamed: JP9.10, U1.13
unnamed: JP9.11, U1.14
RESET: BUTTON.1, C2.1, JP2.1, R2.1, U1.29
RXI: JP1.3, JP9.1, U1.30
TXO: JP1.2, JP9.2, U1.31
VCC: C1.A, C10.1, JP2A1.1, LED1.A, R2.2, REG.5, U1.4, U1.6, U1.18, U$1.PWR, U$1.PWR2

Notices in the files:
parts and their libraries:
SparkFun-Resistors: Licensing: Creative Commons ShareAlike 4.0 International - https://creativecommons.org/licenses/by-sa/4.0
microbuilder: This work is placed in the public domain, and may be freely used for commercial and non-commercial work with the following conditions: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
